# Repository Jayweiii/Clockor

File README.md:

# clockor — POV clock hardware (hybrid v0.6)

Public KiCad 9 design package for a dual-mode clock: a **spinning minute POV LED bar** plus a **slow physical hour hand** on a **coaxial hour shaft**. Jason / `Jayweiii`.

Start with **[docs/design-review-v0.6.md](docs/design-review-v0.6.md)**, then **[docs/architecture.md](docs/architecture.md)**, **[docs/stack-up.md](docs/stack-up.md)**, **[docs/firmware-interlocks.md](docs/firmware-interlocks.md)**, **[docs/pcb-status.md](docs/pcb-status.md)** and **[docs/changelog-review.md](docs/changelog-review.md)**.

## Status

| Area | State |
|---|---|
| Schematics | **v0.6**, regenerated; 0 problems from `scripts/sch_netcheck.py --check`. kicad-cli ERC runs in CI |
| PCBs | **v0.5 layouts, stale.** Need "Update PCB from Schematic" + hand routing. **Do not fabricate** |
| Mechanical CAD | v0.6 coaxial assembly (`cad/`, `renders/mech/`) |
| Firmware | Interlocks specified; code not written |

## Key parts (v0.6)

| Item | Part | Notes |
|------|------|-------|
| Minute BLDC | Hollow-shaft gimbal, 2804 class ~100 KV | 24 V bus; hour shaft passes through the bore |
| Minute encoder | MagAlpha MA730, side-shaft | SPI on `J10` |
| Hour | 28BYJ-48 5 V, coaxial at rear, 1:1 coupler | Only the hour hand is in front of the dial |
| Slip ring | SenRing G012 through-bore brush | 5 V + GND to the rotor |
| Rotor index | DRV5023 | Always-on hall |
| Dial | Clear acrylic | ≥ 5 mm axial gap bar → dial incl. runout |

## Layout

```
hardware/
  base-controller/   ESP32-S3, XL4015 (24→5 V), AMS1117, DRV8313, ULN2003A, USB-C sink + ESD, J9 hour home, J10 encoder
  hand-minute/       ESP32-C3-MINI-1, ME6211, 74AHCT125, 36× APA102-2020, DRV5023, 2×330 µF + TVS, J2 programming
  libs/              Clockor (DRV8313, DRV5023) + Espressif symbols/footprints
cad/                 Coaxial hybrid assembly (CadQuery)
docs/                Design review, architecture, stack-up, interlocks, sources, PCB status
bom/                 Per-board BOM CSVs generated from the schematics
review/              v0.6 net reports; v0.5 ERC/DRC reports and exports (historical)
scripts/             Generator, netlist checker, BOM export, experimental routers
.github/workflows/   KiBot ERC + schematic/BOM exports
```

## Rebuild

```bash
export KICAD9_SYMBOL_DIR=/usr/share/kicad/symbols        # KiCad 9 stock libraries
export KICAD9_FOOTPRINT_DIR=/usr/share/kicad/footprints
python3 scripts/rebuild_boards.py --sch-only             # schematics (+ connectivity check)
python3 scripts/sch_netcheck.py hardware/base-controller/base-controller.kicad_sch --check
python3 scripts/export_bom.py                            # bom/*.csv
python3 cad/build_assembly.py                            # needs cadquery
```

Without `--sch-only` the generator also recreates bare PCB shells for `scripts/place_and_route.py`. That discards the existing layouts.

## License

Public repository for Jason (`Jayweiii`). All rights reserved unless otherwise noted.

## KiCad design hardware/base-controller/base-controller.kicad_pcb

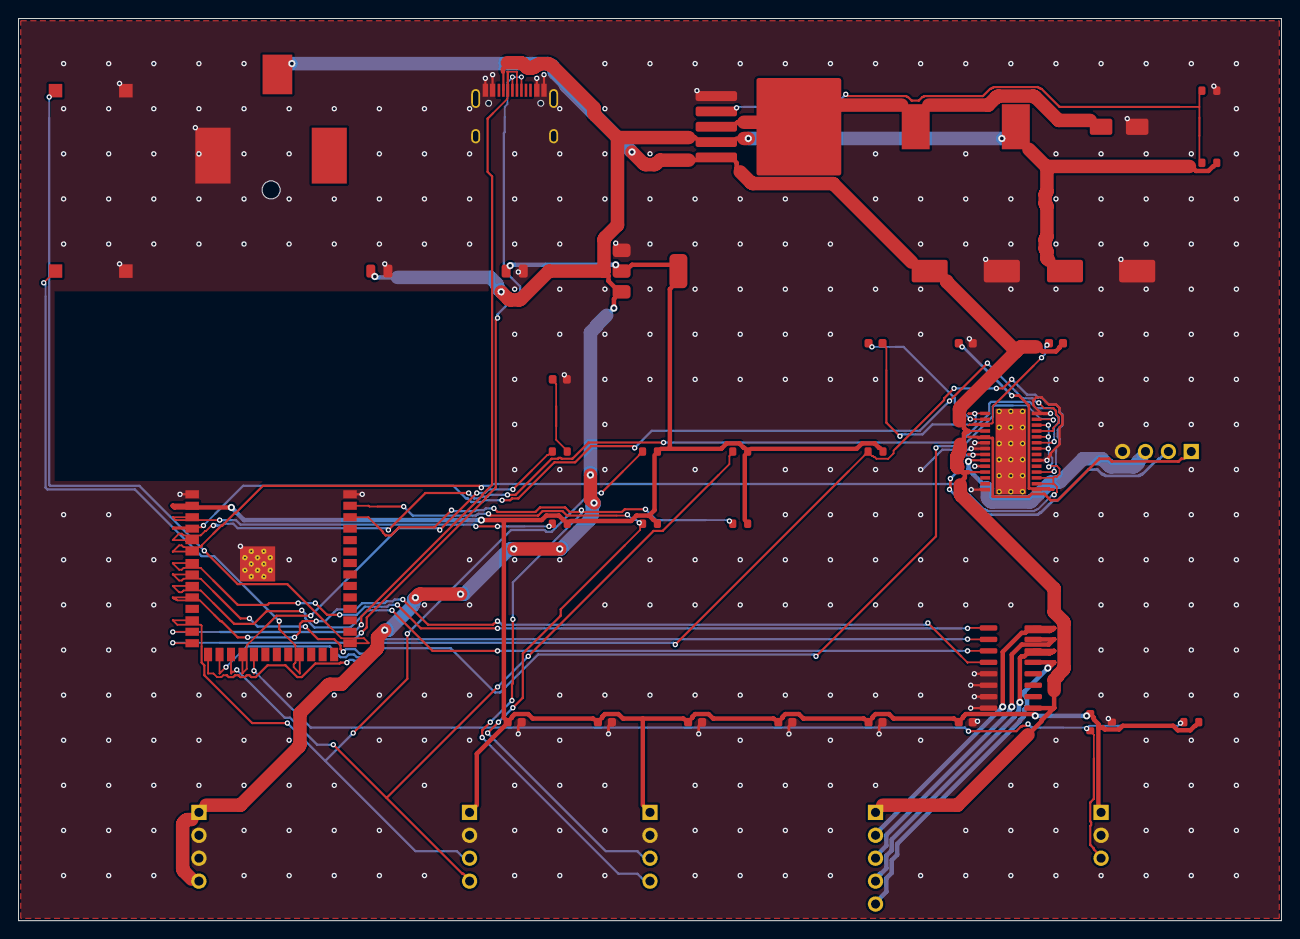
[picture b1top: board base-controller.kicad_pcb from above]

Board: 2 copper layers, 140.0 x 100.0 mm, 42 parts (0 on the bottom side), 38 nets.

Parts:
C1, C2: 470uF; CP_Elec_10x10
C3: 22uF; C_0805_2012Metric
C4: 10uF; C_0805_2012Metric
C10, C11, C12, C13, C14, C15, C21: 100nF; C_0603_1608Metric
C20: 10nF; C_0603_1608Metric
C22: 470nF; C_0603_1608Metric
D1: SS54; D_SMA
D2: LED_R; LED_0603_1608Metric
J1: DC005-2.5; BarrelJack_CUI_PJ-036AH-SMT_Horizontal
J2: TYPE-C-31-M-12; USB_C_Receptacle_HRO_TYPE-C-31-M-12
J3, J5, J6, J7: Conn_01x04; PinHeader_1x04_P2.54mm_Vertical
J8: Conn_01x05; PinHeader_1x05_P2.54mm_Vertical
J9: Conn_01x03; PinHeader_1x03_P2.54mm_Vertical
L1: 47uH; L_TaiTech_TMPC1265_13.5x12.5mm
R1, R4: 1k; R_0603_1608Metric
R2, R3, R6, R7: 4.7k; R_0603_1608Metric
R5: 3.00k; R_0603_1608Metric
R20, R21, R22: 10k; R_0603_1608Metric
SW1: BOOT; SW_SPST_CK_RS282G05A3
SW2: MODE; SW_SPST_CK_RS282G05A3
U1: ESP32-S3-WROOM-1-N16R8; ESP32-S3-WROOM-1
U2: XL4015E1; TO-263-5_TabPin3
U3: AMS1117-3.3; SOT-223-3_TabPin2
U4: ULN2003ADR; SOIC-16_3.9x9.9mm_P1.27mm
U5: DRV8313PWPR; HTSSOP-28-1EP_4.4x9.7mm_P0.65mm_EP3.4x9.5mm_ThermalVias
U6: AH1806-W-7; SC-59

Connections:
+3V3: C3.1, C10.1, C11.1, C12.1, C13.1, C14.1, C15.1, J5.1, J6.1, J9.1, R2.2, R3.2, R6.2, R7.2, R20.2, R21.2, R22.2, U1.2, U3.2, U6.1
+5V: C2.1, C4.1, J2.A5, J7.1, J7.4, L1.2, R5.2, U2.4, U3.3
/BOOT: SW1.1, U1.27
/BUCK_FB: R4.1, R5.1, U2.2
/BUCK_SW: D1.1, L1.1, U2.3
/EN_ESP: R20.1, U1.3
/HR_HOME: J9.3, R22.1, U1.19, U6.2
/HR_IN1: U1.7, U4.1
/HR_IN2: U1.8, U4.2
/HR_IN3: U1.9, U4.3
/HR_IN4: U1.10, U4.4
/HR_OUT1: J8.2, U4.16
/HR_OUT2: J8.3, U4.15
/HR_OUT3: J8.4, U4.14
/HR_OUT4: J8.5, U4.13
/I2C0_SCL: J5.4, R3.1, U1.17
/I2C0_SDA: J5.3, R2.1, U1.12
/I2C1_SCL: J6.4, R7.1, U1.38
/I2C1_SDA: J6.3, R6.1, U1.39
/LED_K: D2.1, R1.2
/M1_CPH: C20.1, U5.2
/M1_CPL: C20.2, U5.1
/M1_EN1: U1.6, U5.16, U5.17, U5.22, U5.24, U5.26
/M1_IN1: U1.15, U5.27
/M1_IN2: U1.4, U5.25
/M1_IN3: U1.5, U5.23
/M1_OUTA: J3.1, U5.5
/M1_OUTB: J3.2, U5.8
/M1_OUTC: J3.3, U5.9
/M1_V3P3: C22.1, U5.15
/M1_VCP: C21.1, U5.3
/M1_nFAULT: R21.1, U1.16, U5.18
/MODE_BTN: SW2.1, U1.23
/STATUS_LED: R1.1, U1.18
/USB_D+: J2.A6, J2.B6, U1.14
/USB_D-: J2.A7, J2.B7, U1.13
/VIN_12V: C1.1, C21.2, J1.1, J8.1, U2.5, U4.9, U5.4, U5.11
GND: C1.2, C2.2, C3.2, C4.2, C10.2, C11.2, C12.2, C13.2, C14.2, C15.2, C22.2, D1.2, D2.2, J1.2, J2.A1, J2.A4, J2.A9, J2.A12, J2.B1, J2.B4, J2.B9, J2.B12, J2.S1, J3.4, J5.2, J6.2, J7.2, J7.3, J9.2, R4.2, SW1.2, SW2.2, U1.1, U1.40, U1.41, U2.1, U3.1, U4.5, U4.6, U4.7, U4.8, U5.6, U5.7, U5.10, U5.14, U5.20, U5.28, U6.3

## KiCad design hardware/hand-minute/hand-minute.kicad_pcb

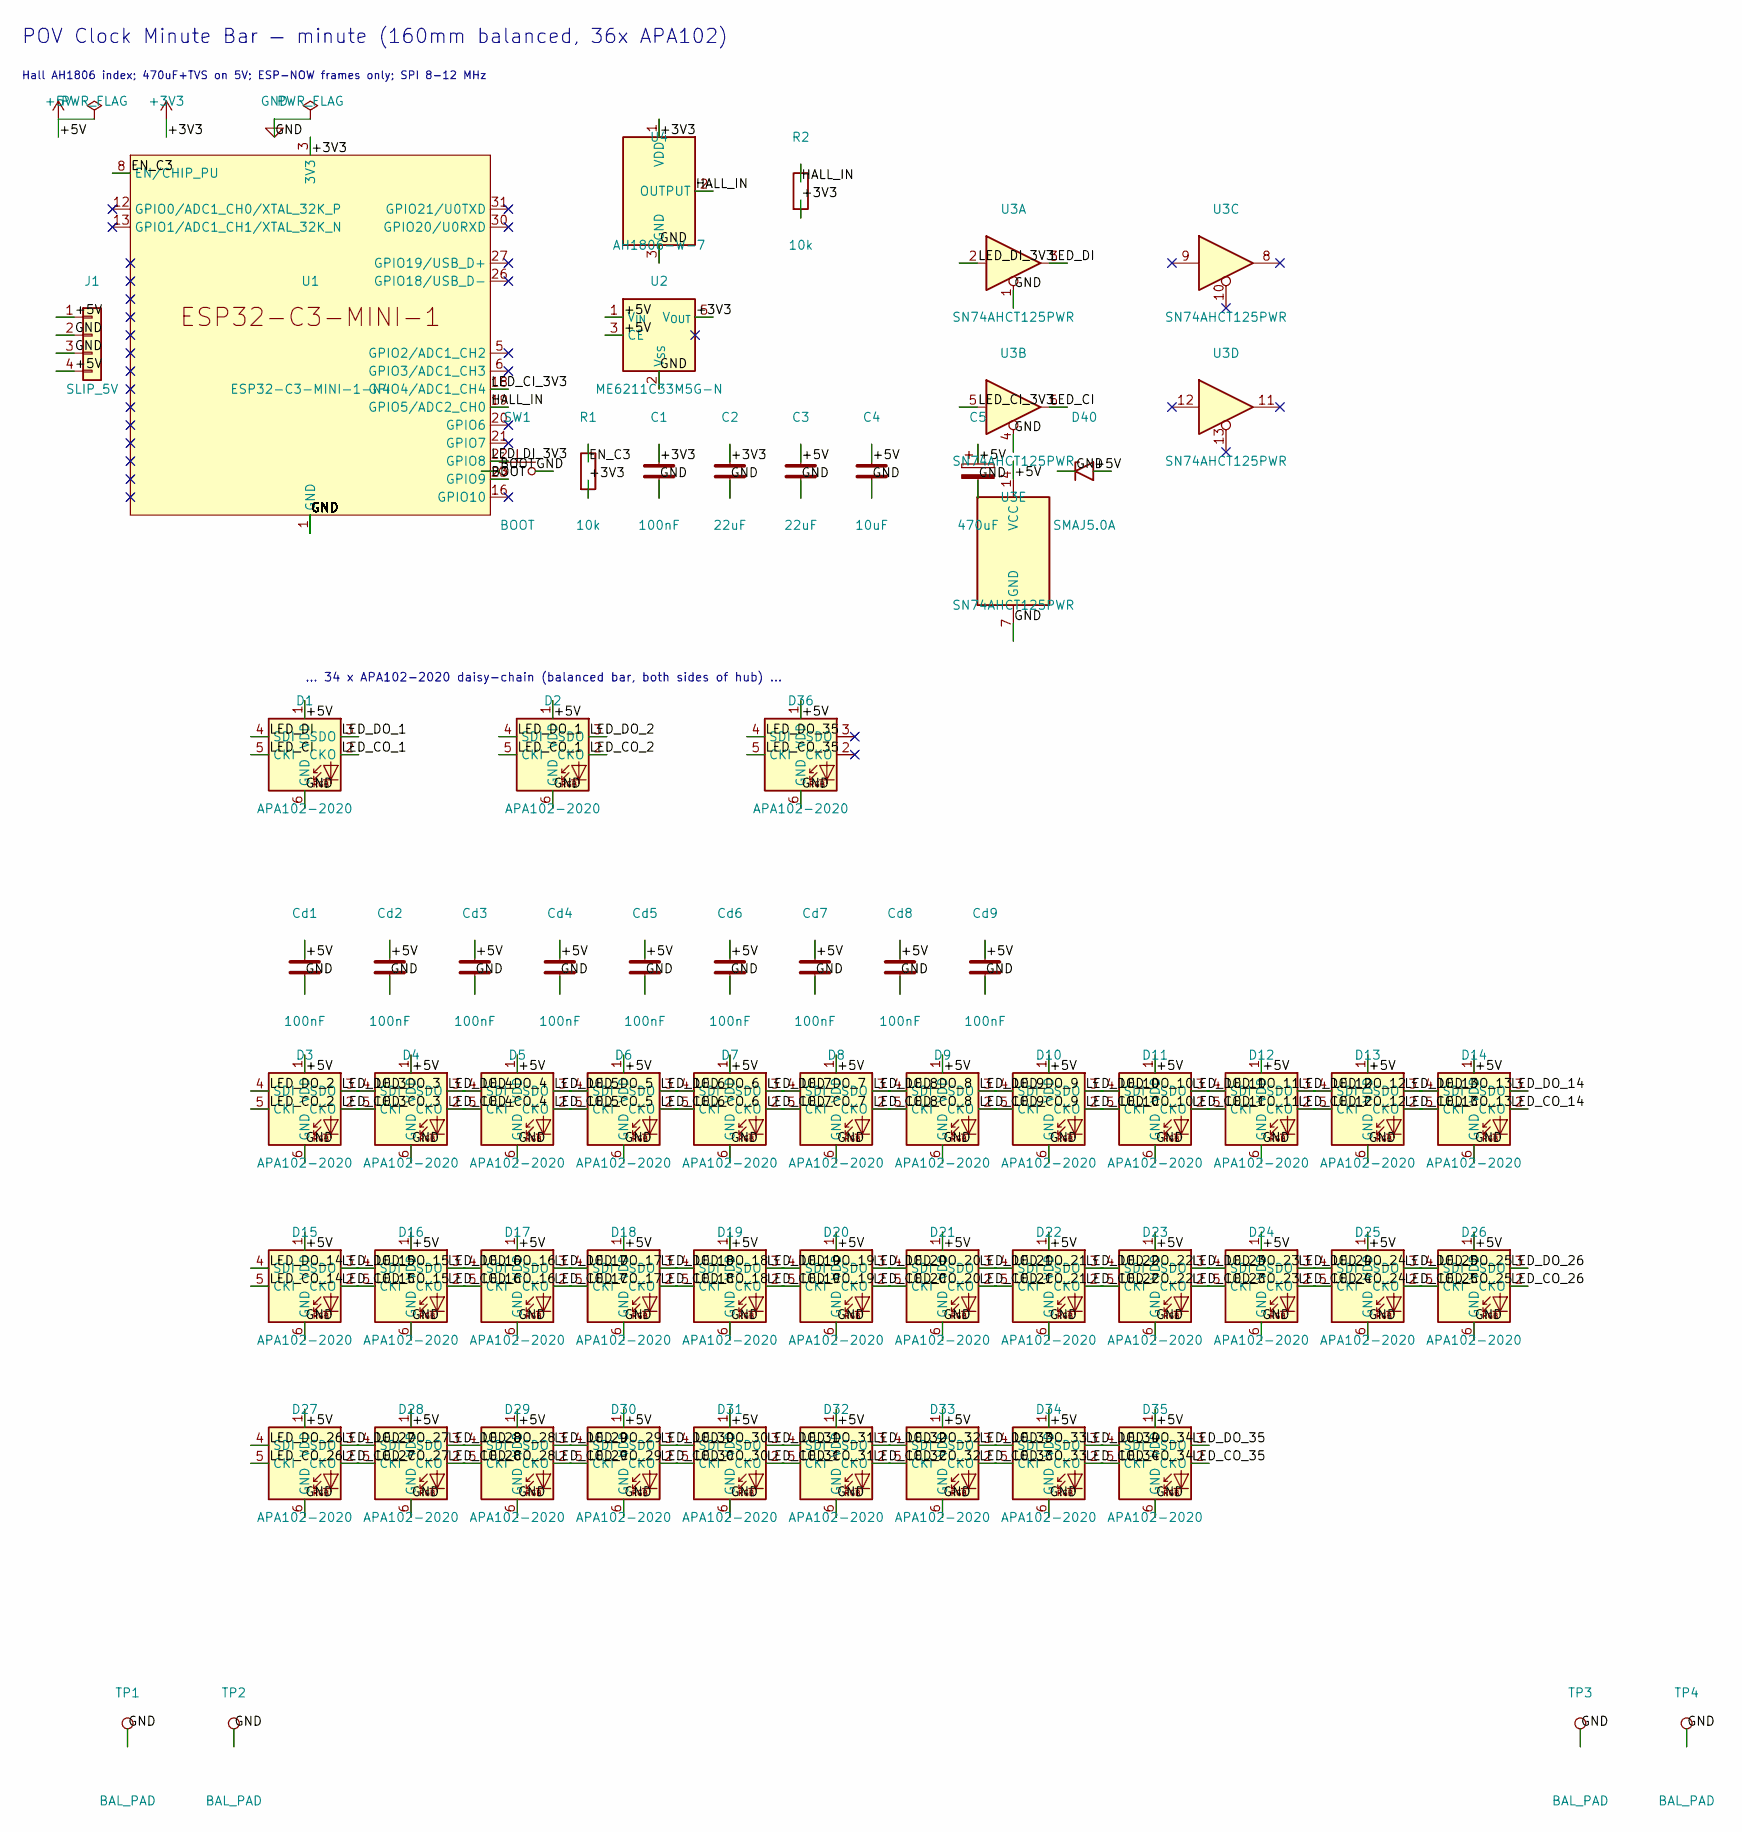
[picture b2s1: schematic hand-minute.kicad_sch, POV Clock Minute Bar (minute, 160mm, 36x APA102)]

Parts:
C1: 100nF; C_0603_1608Metric
C2, C3: 22uF; C_0805_2012Metric
C4: 10uF; C_0805_2012Metric
C5: 470uF; CP_Elec_10x10
Cd1, Cd2, Cd3, Cd4, Cd5, Cd6, Cd7, Cd8, Cd9: 100nF; C_0603_1608Metric
D1, D2, D3, D4, D5, D6, D7, D8, D9, D10, D11, D12, D13, D14, D15, D16, D17, D18, D19, D20, D21, D22, D23, D24, D25, D26, D27, D28, D29, D30, D31, D32, D33, D34, D35, D36: APA102-2020; LED-APA102-2020
D40: SMAJ5.0A; D_SMA
J1: SLIP_5V; PinHeader_1x04_P2.54mm_Vertical
R1, R2: 10k; R_0603_1608Metric
SW1: BOOT; SW_SPST_CK_RS282G05A3
TP1, TP2, TP3, TP4: BAL_PAD; TestPoint_Pad_D2.5mm
U1: ESP32-C3-MINI-1-N4; ESP32-C3-MINI-1
U2: ME6211C33M5G-N; SOT-23-5
U3: SN74AHCT125PWR; TSSOP-14_4.4x5mm_P0.65mm
U4: AH1806-W-7; SC-59

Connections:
+3V3: C1.1, C2.1, R1.2, R2.2, U1.3 (3V3), U2.5 (V_{OUT}), U4.1 (VDD)
+5V: C3.1, C4.1, C5.1, Cd1.1, Cd2.1, Cd3.1, Cd4.1, Cd5.1, Cd6.1, Cd7.1, Cd8.1, Cd9.1, D1.1 (VDD), D2.1 (VDD), D3.1 (VDD), D4.1 (VDD), D5.1 (VDD), D6.1 (VDD), D7.1 (VDD), D8.1 (VDD), D9.1 (VDD), D10.1 (VDD), D11.1 (VDD), D12.1 (VDD), D13.1 (VDD), D14.1 (VDD), D15.1 (VDD), D16.1 (VDD), D17.1 (VDD), D18.1 (VDD), D19.1 (VDD), D20.1 (VDD), D21.1 (VDD), D22.1 (VDD), D23.1 (VDD), D24.1 (VDD), D25.1 (VDD), D26.1 (VDD), D27.1 (VDD), D28.1 (VDD), D29.1 (VDD), D30.1 (VDD), D31.1 (VDD), D32.1 (VDD), D33.1 (VDD), D34.1 (VDD), D35.1 (VDD), D36.1 (VDD), D40.2 (A2), J1.1, J1.4, U2.1 (V_{IN}), U2.3 (CE), U3.14 (VCC)
/BOOT: SW1.1, U1.23 (GPIO9)
/EN_C3: R1.1, U1.8 (EN/CHIP_PU)
/HALL_IN: R2.1, U1.19 (GPIO5/ADC2_CH0), U4.2 (OUTPUT)
/LED_CI: D1.5 (CKI), U3.6
/LED_CI_3V3: U1.18 (GPIO4/ADC1_CH4), U3.5
/LED_CO_1: D1.2 (CKO), D2.5 (CKI)
/LED_CO_2: D2.2 (CKO), D3.5 (CKI)
/LED_CO_3: D3.2 (CKO), D4.5 (CKI)
/LED_CO_4: D4.2 (CKO), D5.5 (CKI)
/LED_CO_5: D5.2 (CKO), D6.5 (CKI)
/LED_CO_6: D6.2 (CKO), D7.5 (CKI)
/LED_CO_7: D7.2 (CKO), D8.5 (CKI)
/LED_CO_8: D8.2 (CKO), D9.5 (CKI)
/LED_CO_9: D9.2 (CKO), D10.5 (CKI)
/LED_CO_10: D10.2 (CKO), D11.5 (CKI)
/LED_CO_11: D11.2 (CKO), D12.5 (CKI)
/LED_CO_12: D12.2 (CKO), D13.5 (CKI)
/LED_CO_13: D13.2 (CKO), D14.5 (CKI)
/LED_CO_14: D14.2 (CKO), D15.5 (CKI)
/LED_CO_15: D15.2 (CKO), D16.5 (CKI)
/LED_CO_16: D16.2 (CKO), D17.5 (CKI)
/LED_CO_17: D17.2 (CKO), D18.5 (CKI)
/LED_CO_18: D18.2 (CKO), D19.5 (CKI)
/LED_CO_19: D19.2 (CKO), D20.5 (CKI)
/LED_CO_20: D20.2 (CKO), D21.5 (CKI)
/LED_CO_21: D21.2 (CKO), D22.5 (CKI)
/LED_CO_22: D22.2 (CKO), D23.5 (CKI)
/LED_CO_23: D23.2 (CKO), D24.5 (CKI)
/LED_CO_24: D24.2 (CKO), D25.5 (CKI)
/LED_CO_25: D25.2 (CKO), D26.5 (CKI)
/LED_CO_26: D26.2 (CKO), D27.5 (CKI)
/LED_CO_27: D27.2 (CKO), D28.5 (CKI)
/LED_CO_28: D28.2 (CKO), D29.5 (CKI)
/LED_CO_29: D29.2 (CKO), D30.5 (CKI)
/LED_CO_30: D30.2 (CKO), D31.5 (CKI)
/LED_CO_31: D31.2 (CKO), D32.5 (CKI)
/LED_CO_32: D32.2 (CKO), D33.5 (CKI)
/LED_CO_33: D33.2 (CKO), D34.5 (CKI)
/LED_CO_34: D34.2 (CKO), D35.5 (CKI)
/LED_CO_35: D35.2 (CKO), D36.5 (CKI)
/LED_DI: D1.4 (SDI), U3.3
/LED_DI_3V3: U1.22 (GPIO8), U3.2
/LED_DO_1: D1.3 (SDO), D2.4 (SDI)
/LED_DO_2: D2.3 (SDO), D3.4 (SDI)
/LED_DO_3: D3.3 (SDO), D4.4 (SDI)
/LED_DO_4: D4.3 (SDO), D5.4 (SDI)
/LED_DO_5: D5.3 (SDO), D6.4 (SDI)
/LED_DO_6: D6.3 (SDO), D7.4 (SDI)
/LED_DO_7: D7.3 (SDO), D8.4 (SDI)
/LED_DO_8: D8.3 (SDO), D9.4 (SDI)
/LED_DO_9: D9.3 (SDO), D10.4 (SDI)
/LED_DO_10: D10.3 (SDO), D11.4 (SDI)
/LED_DO_11: D11.3 (SDO), D12.4 (SDI)
/LED_DO_12: D12.3 (SDO), D13.4 (SDI)
/LED_DO_13: D13.3 (SDO), D14.4 (SDI)
/LED_DO_14: D14.3 (SDO), D15.4 (SDI)
/LED_DO_15: D15.3 (SDO), D16.4 (SDI)
/LED_DO_16: D16.3 (SDO), D17.4 (SDI)
/LED_DO_17: D17.3 (SDO), D18.4 (SDI)
/LED_DO_18: D18.3 (SDO), D19.4 (SDI)
/LED_DO_19: D19.3 (SDO), D20.4 (SDI)
/LED_DO_20: D20.3 (SDO), D21.4 (SDI)
/LED_DO_21: D21.3 (SDO), D22.4 (SDI)
/LED_DO_22: D22.3 (SDO), D23.4 (SDI)
/LED_DO_23: D23.3 (SDO), D24.4 (SDI)
/LED_DO_24: D24.3 (SDO), D25.4 (SDI)
/LED_DO_25: D25.3 (SDO), D26.4 (SDI)
/LED_DO_26: D26.3 (SDO), D27.4 (SDI)
/LED_DO_27: D27.3 (SDO), D28.4 (SDI)
/LED_DO_28: D28.3 (SDO), D29.4 (SDI)
/LED_DO_29: D29.3 (SDO), D30.4 (SDI)
/LED_DO_30: D30.3 (SDO), D31.4 (SDI)
/LED_DO_31: D31.3 (SDO), D32.4 (SDI)
/LED_DO_32: D32.3 (SDO), D33.4 (SDI)
/LED_DO_33: D33.3 (SDO), D34.4 (SDI)
/LED_DO_34: D34.3 (SDO), D35.4 (SDI)
/LED_DO_35: D35.3 (SDO), D36.4 (SDI)
GND: C1.2, C2.2, C3.2, C4.2, C5.2, Cd1.2, Cd2.2, Cd3.2, Cd4.2, Cd5.2, Cd6.2, Cd7.2, Cd8.2, Cd9.2, D1.6 (GND), D2.6 (GND), D3.6 (GND), D4.6 (GND), D5.6 (GND), D6.6 (GND), D7.6 (GND), D8.6 (GND), D9.6 (GND), D10.6 (GND), D11.6 (GND), D12.6 (GND), D13.6 (GND), D14.6 (GND), D15.6 (GND), D16.6 (GND), D17.6 (GND), D18.6 (GND), D19.6 (GND), D20.6 (GND), D21.6 (GND), D22.6 (GND), D23.6 (GND), D24.6 (GND), D25.6 (GND), D26.6 (GND), D27.6 (GND), D28.6 (GND), D29.6 (GND), D30.6 (GND), D31.6 (GND), D32.6 (GND), D33.6 (GND), D34.6 (GND), D35.6 (GND), D36.6 (GND), D40.1 (A1), J1.2, J1.3, SW1.2, TP1.1, TP2.1, TP3.1, TP4.1, U1.1 (GND), U1.2 (GND), U1.11 (GND), U1.14 (GND), U1.36 (GND), U1.37 (GND), U1.38 (GND), U1.39 (GND), U1.40 (GND), U1.41 (GND), U1.42 (GND), U1.43 (GND), U1.44 (GND), U1.45 (GND), U1.46 (GND), U1.47 (GND), U1.48 (GND), U1.49 (GND), U1.50 (GND), U1.51 (GND), U1.52 (GND), U1.53 (GND), U2.2 (V_{SS}), U3.1, U3.4, U3.7 (GND), U4.3 (GND)

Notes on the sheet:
... 34 x APA102-2020 daisy-chain (balanced bar, both sides of hub) ...
POV Clock Minute Bar — minute (160mm balanced, 36x APA102)
Hall AH1806 index; 470uF+TVS on 5V; ESP-NOW frames only; SPI 8-12 MHz

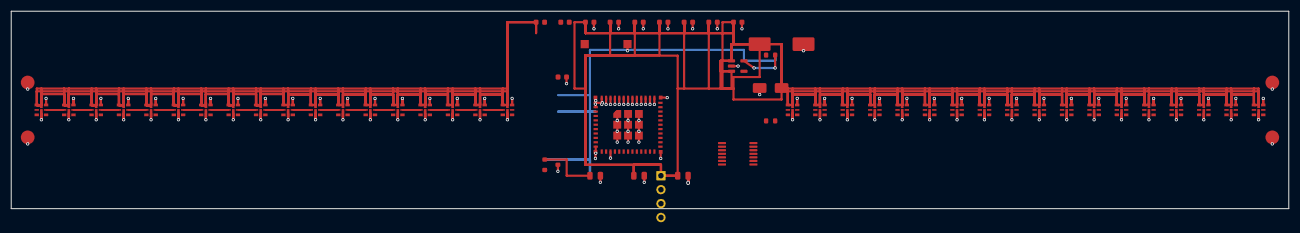
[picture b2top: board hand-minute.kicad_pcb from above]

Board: 2 copper layers, 233.0 x 36.0 mm, 63 parts (0 on the bottom side), 80 nets.

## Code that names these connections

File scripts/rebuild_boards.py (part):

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        if pn in esp_pos:
            parts.append(connect_label_to_pin(net, esp_pos[pn]))
    if "3" in esp_pos:
        parts.append(connect_label_to_pin("EN_ESP", esp_pos["3"]))
    for pn, net in [("13", "USB_D-"), ("14", "USB_D+")]:
        if pn in esp_pos:
            parts.append(connect_label_to_pin(net, esp_pos[pn]))
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        parts.append(connect_label_to_pin("BOOT", esp_pos["27"]))

    # I2C0 → AS5600 minute encoder (no mux). I2C1 reserved / header.
    # Espressif WROOM-1: pin12=GPIO8 SDA-ish, pin17=GPIO9 SCL (same as prior)
    for pn, net in [("12", "I2C0_SDA"), ("17", "I2C0_SCL")]:
        if pn in esp_pos:
            parts.append(connect_label_to_pin(net, esp_pos[pn]))
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
    # WROOM-1 pad → GPIO (v0.6). Strapping pins GPIO0/3/45/46 carry nothing that
    # pulls them the wrong way at reset; GPIO35-37 are reserved for octal PSRAM (N16R8).
    #   pad 15 GPIO3  M1_IN1   | pad 4 GPIO4 M1_IN2 | pad 5 GPIO5 M1_IN3
    #   pad 6  GPIO6  M1_EN_ALL (EN1-3, 10k pull-down → bridges off at boot)
    #   pad 31 GPIO38 M1_nSLEEP (nSLEEP+nRESET, 10k pull-down → driver asleep at boot)
    #   pad 11 GPIO18 M1_nFAULT (was GPIO46: pull-up on a strap pin blocked download mode)
    #   pads 7-10 GPIO7/15/16/17 HR_IN1-4 | pad 19 GPIO11 HR_HOME
    #   pads 20/21/22/32 GPIO12/13/14/39 encoder SPI (SCK/MISO/MOSI/CS)
    gpio_map = [
        ("15", "M1_IN1"), ("4", "M1_IN2"), ("5", "M1_IN3"), ("6", "M1_EN_ALL"),
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    # Hour home: remote hall on the rear hour-shaft coupler (magnet on coupler) via J9.
    # v0.5 also had U6 on this PCB — it could never see the magnet and sat in
    # parallel with J9, so it is removed. R22 pull-up for an open-drain sensor.
    two_pin("R", "R22", "10k", (200.0, 160.0), FP["R"], "HR_HOME", "+3V3")
    hdr("J9", (220.0, 160.0), ["+3V3", "GND", "HR_HOME"], "Conn_01x03", "HDR3")
    two_pin("C", "C26", "100nF", (235.0, 160.0), FP["C"], "HR_HOME", "GND")  # cable noise filter

    # USB-C support: Rd on CC, ESD array, VBUS OR-ing diode
    two_pin("R", "R23", "5.1k", (20.0, 95.0), FP["R"], "USB_CC1", "GND")
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    parts.append(label("SLIP_GND", 110, 155))

    # Passives
    two_pin("L", "L1", "47uH", (45.0, 130.0), FP["L"], "BUCK_SW", "+5V")
    two_pin("D", "D1", "SS54", (55.0, 130.0), FP["D"], "BUCK_SW", "GND")
    two_pin("C_Polarized", "C1", "470uF 35V", (25.0, 130.0), FP["CP"], "VIN_24V", "GND")
    two_pin("C", "C27", "1uF 50V", (35.0, 150.0), FP["C0805"], "BUCK_VC", "VIN_24V")
    two_pin("C_Polarized", "C2", "470uF", (65.0, 130.0), FP["CP"], "+5V", "GND")
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    for i, ref in enumerate(["C10", "C11", "C12", "C13", "C14", "C15"]):
        two_pin("C", ref, "100nF", (110.0 + i * 10, 160.0), FP["C"], "+3V3", "GND")

    two_pin("R", "R1", "1k", (50.0, 90.0), FP["R"], "STATUS_LED", "LED_K")
    two_pin("LED", "D2", "LED_R", (60.0, 90.0), FP["LED"], "LED_K", "GND")
    two_pin("R", "R2", "4.7k", (120.0, 90.0), FP["R"], "I2C0_SDA", "+3V3")
    two_pin("R", "R3", "4.7k", (130.0, 90.0), FP["R"], "I2C0_SCL", "+3V3")
    two_pin("R", "R4", "1k", (40.0, 140.0), FP["R"], "BUCK_FB", "GND")
    two_pin("R", "R5", "3.00k", (50.0, 140.0), FP["R"], "BUCK_FB", "+5V")
    two_pin("R", "R20", "10k", (40.0, 90.0), FP["R"], "EN_ESP", "+3V3")
    two_pin("R", "R21", "10k", (250.0, 30.0), FP["R"], "M1_nFAULT", "+3V3")
    two_pin("R", "R6", "4.7k", (150.0, 90.0), FP["R"], "I2C1_SDA", "+3V3")
    two_pin("R", "R7", "4.7k", (160.0, 90.0), FP["R"], "I2C1_SCL", "+3V3")

    # Buttons spaced ≥ 20 mm: v0.5 put SW1 pin 2 and SW2 pin 1 0.16 mm apart.
    two_pin("SW_Push", "SW1", "BOOT", (70.0, 90.0), FP["SW"], "BOOT", "GND")
    two_pin("SW_Push", "SW2", "MODE", (90.0, 90.0), FP["SW"], "MODE_BTN", "GND")

    # DRV8313 control: EN1-3 together (GPIO6), nSLEEP+nRESET together (GPIO38).
    # Both pulled low so the bridge is off/asleep while the S3 boots or resets.
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    two_pin("R", "R26", "10k", (285.0, 200.0), FP["R"], "M1_nSLEEP", "GND")

    # Charge-pump caps (KiBot-safe refs)
    two_pin("C", "C20", "10nF", (250, 170), FP["C"], "M1_CPH", "M1_CPL")
    two_pin("C", "C21", "100nF", (250, 180), FP["C"], "M1_VCP", "VIN_24V")
    two_pin("C", "C22", "470nF", (250, 190), FP["C"], "M1_V3P3", "GND")
    # VM local decoupling at DRV8313 pins 4 and 11 (v0.5 relied on C1 only)
    two_pin("C", "C23", "100nF 50V", (250, 210), FP["C"], "VIN_24V", "GND")
    two_pin("C", "C24", "100nF 50V", (260, 210), FP["C"], "VIN_24V", "GND")
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    for pn, net in [
        ("3", "+3V3"), ("1", "GND"), ("2", "GND"), ("11", "GND"), ("14", "GND"),
        ("8", "EN_C3"), ("23", "BOOT"),
        ("22", "LED_DI_3V3"),  # GPIO8 DI — SPI-ish ~10 MHz in FW (strap: 10k pull-up R3)
        ("18", "LED_CI_3V3"),  # GPIO4 CI
        ("19", "HALL_IN"),     # GPIO5 — once-per-rev index
        ("5", "C3_GPIO2"),     # strap: 10k pull-up R4
        # Programming access (v0.5 had none): UART0 on J2, native USB on TP5/TP6
        ("30", "C3_RXD"), ("31", "C3_TXD"),
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    for pn, net in [("1", "+3V3"), ("2", "HALL_IN"), ("3", "GND")]:
        if pn in hp:
            parts.append(connect_label_to_pin(net, hp[pn]))
    two_pin("R", "R2", "10k", (120.0, 30.48), FP["R"], "HALL_IN", "+3V3")

    # APA102 chain
    def place_led(ref, xy, di, ci, do, co):
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    # v0.5 had pin 1 on GND → TVS forward-biased across the rail (dead short).
    two_pin("SMAJ5.0A", "D40", "SMAJ5.0A", (160, 70), FP["SMAJ5.0A"], "+5V", "GND")

    two_pin("R", "R1", "10k", (90, 70), FP["R"], "EN_C3", "+3V3")
    two_pin("C", "C6", "1uF", (90, 90), FP["C"], "EN_C3", "GND")  # EN RC delay per Espressif HW guide
    two_pin("R", "R3", "10k", (70, 90), FP["R"], "LED_DI_3V3", "+3V3")  # GPIO8 strap high
    two_pin("R", "R4", "10k", (80, 90), FP["R"], "C3_GPIO2", "+3V3")    # GPIO2 strap high
    two_pin("SW_Push", "SW1", "BOOT", (80, 70), FP["SW"], "BOOT", "GND")

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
